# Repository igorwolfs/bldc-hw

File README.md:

# bldc

### NOTES
Replace the high power resistors C25468, minimum order quantity is 400+

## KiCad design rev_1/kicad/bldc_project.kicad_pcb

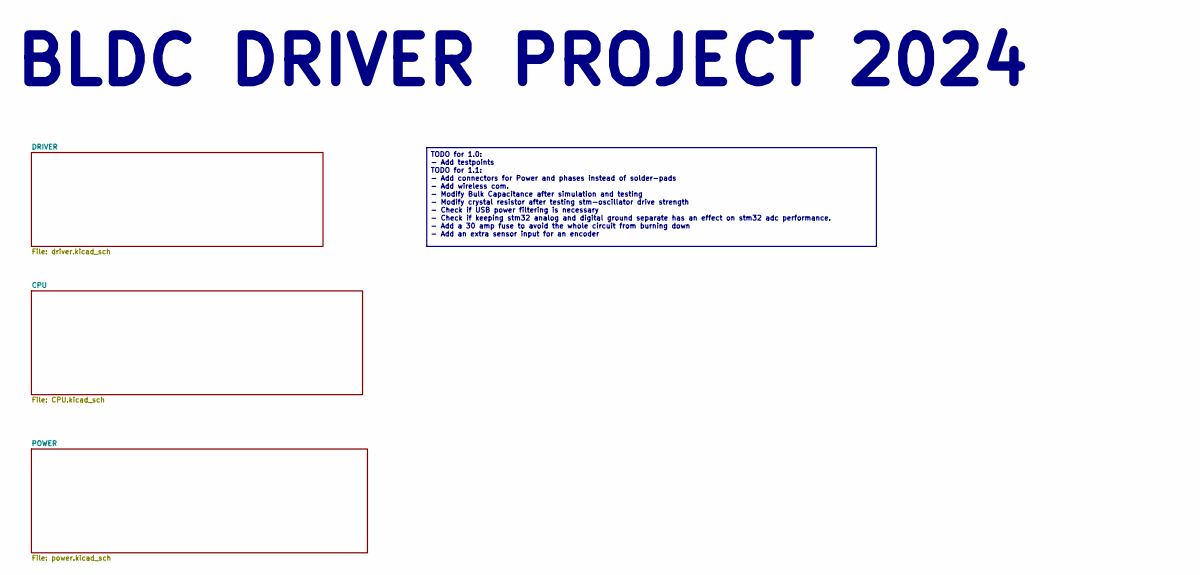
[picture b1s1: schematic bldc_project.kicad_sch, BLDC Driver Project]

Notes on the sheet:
BLDC DRIVER PROJECT 2024
TODO for 1.0: - Add testpoints TODO for 1.1: - Add connectors for Power and phases instead of solder-pads - Add wireless com. - Modify Bulk Capacitance after simulation and testing - Modify crystal resistor after testing stm-oscillator drive strength - Check if USB power filtering is necessary - Ch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

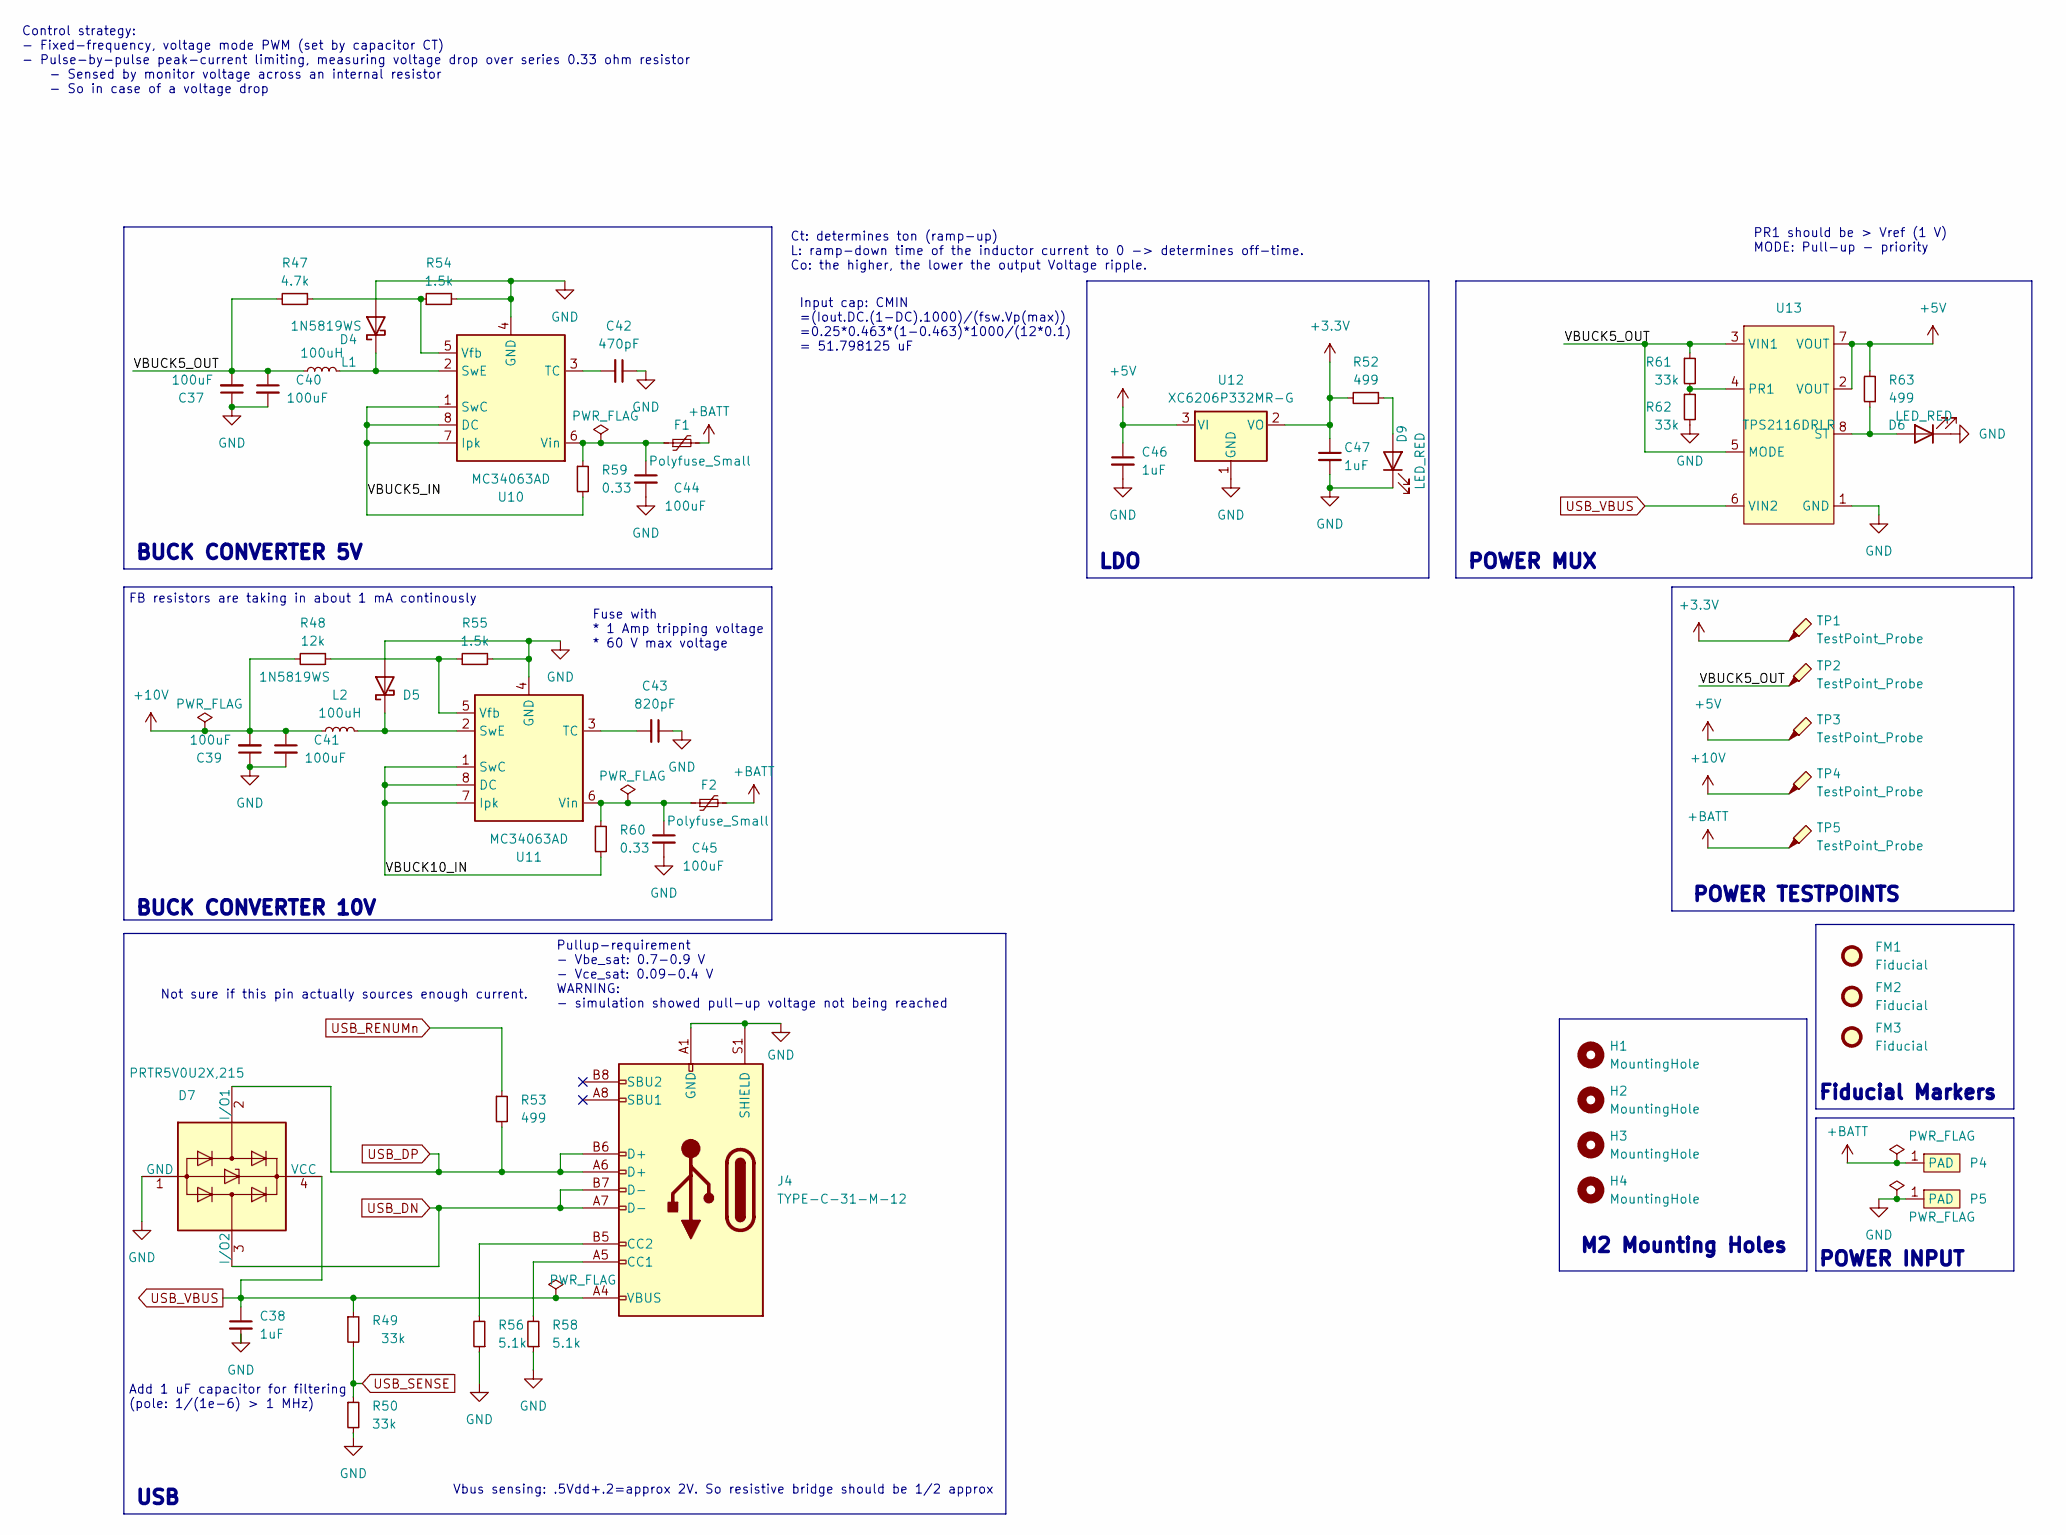
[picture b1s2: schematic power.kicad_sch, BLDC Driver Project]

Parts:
C37, C39, C40, C41, C44, C45: 100uF; C_1210_3225Metric; Manufacturing part numb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 CA55-B6R3M107T; LCSC Part Number C568913
C38, C46, C47: 1uF; C_1206_3216Metric; Manufacturing part numb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 CL31B105KBHNNNE; LCSC Part Number C1848
C42: 470pF; C_0603_1608Metric; Manufacturing part numb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 0603B471K500NT; LCSC Part Number C1620
C43: 820pF; C_0805_2012Metric_Pad1.18x1.45mm_HandSolder; Manufacturing part numb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 CL21B821KBANNNC; LCSC Part Number C296722
D4, D5: 1N5819WS; D_SOD-323; Manufacturing part numb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 1N5819WS; LCSC Part Number C191023
D6, D9: LED_RED; LED_0603_1608Metric; Manufacturing part numb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 F.0603.00139/P2-0603R1TS2-06T-002; LCSC Part Number C7496820
D7: PRTR5V0U2X,215; SOT-143; Manufacturing part numb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 PRTR5V0U2X,215; LCSC Part Number C12333
F1, F2: Polyfuse_Small; Fuse_1812_4532Metric; Manufacturing part numb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 BSMD1812-050-60V; LCSC Part Number C883142
FM1, FM2, FM3: Fiducial; Fiducial_1mm_Mask2mm
H1, H2, H3, H4: MountingHole; MountingHole_1.152mm_jlcpcb
J4: TYPE-C-31-M-12; USB_C_Receptacle_HRO_TYPE-C-31-M-12; Manufacturing part numb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 TYPE-C-31-M-12; LCSC Part Number C165948
L1, L2: 100uH; L_Sunlord_SWPA6045S; Manufacturing part numb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 SWPA6045S101MT; LCSC Part Number C60633
P4, P5: SolderWirePad_1x01_SMD_5x10mm
R47: 4.7k; R_0805_2012Metric; Manufacturing part numb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 0805W8F4701T5E; LCSC Part Number C17673
R48: 12k; R_0603_1608Metric; Manufacturing part numb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 0603WAF1202T5E; LCSC Part Number C22790
R49, R50, R61, R62: 33k; R_0603_1608Metric; Manufacturing part numb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 0603WAF3302T5E; LCSC Part Number C4216
R52, R53, R63: 499; R_0402_1005Metric; Manufacturing part numb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 0402WGF4990TCE; LCSC Part Number C4125
R54, R55: 1.5k; R_0805_2012Metric; Manufacturing part numb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 0805W8F1501T5E; LCSC Part Number C4310
R56, R58: 5.1k; R_0805_2012Metric; Manufacturing part numb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 0805W8F5101T5E; LCSC Part Number C27834
R59, R60: 0.33; R_1206_3216Metric; Manufacturing part numb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 1206W4J033KT5E; LCSC Part Number C25347
TP1, TP2, TP3, TP4, TP5: TestPoint_Probe; TestPoint_THTPad_D1.0mm_Drill0.5mm
U10, U11: MC34063AD; SOIC-8_3.9x4.9mm_P1.27mm; Manufacturing part numb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 MC34063; LCSC Part Number C5349988
U12: XC6206P332MR-G; SOT-23; Manufacturing part numb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 XC6206P332MR-G; LCSC Part Number C5446
U13: TPS2116DRLR; SOT-583-8; Manufacturing part numb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 TPS2116DRLR; LCSC Part Number C3235557

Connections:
+3.3V: C47.1, R52.2, TP1.1, U12.2 (VO); also elsewhere on the board
+5V: C46.1, R63.2, TP3.1, U12.3 (VI), U13.2 (VOUT), U13.7 (VOUT); also elsewhere on the board
+10V: C39.2, C41.1, L2.1, R48.2, TP4.1; also elsewhere on the board
+BATT: F1.2, F2.2, P4.1 (PAD), TP5.1; also elsewhere on the board
/POWER/VBUCK5_IN: R59.2, U10.1 (SwC), U10.7 (Ipk), U10.8 (DC)
/POWER/VBUCK5_OUT: C37.2, C40.1, L1.1, R47.2, R61.1, TP2.1, U13.3 (VIN1), U13.5 (MODE)
/POWER/VBUCK10_IN: R60.2, U11.1 (SwC), U11.7 (Ipk), U11.8 (DC)
GND: C37.1, C38.2, C39.1, C40.2, C41.2, C42.1, C43.1, C44.2, C45.2, C46.2, C47.2, D4.2 (A), D5.2 (A), D6.1 (K), D7.1 (GND), D9.1 (K), J4.A1 (GND), J4.A12 (GND), J4.B1 (GND), J4.B12 (GND), J4.S1 (SHIELD), P5.1 (PAD), R50.2, R54.2, R55.2, R56.1, R58.1, R62.2, U10.4 (GND), U11.4 (GND), U12.1 (GND), U13.1 (GND); also elsewhere on the board
unnamed: D4.1 (K), L1.2, U10.2 (SwE)
unnamed: D5.1 (K), L2.2, U11.2 (SwE)
unnamed: D6.2 (A), R63.1, U13.8 (ST)
unnamed: D9.2 (A), R52.1
unnamed: J4.A5 (CC1), R58.2
unnamed: J4.B5 (CC2), R56.2
unnamed: C42.2, U10.3 (TC)
unnamed: R47.1, R54.1, U10.5 (Vfb)
unnamed: C44.1, F1.1, R59.1, U10.6 (Vin)
unnamed: C43.2, U11.3 (TC)
unnamed: R48.1, R55.1, U11.5 (Vfb)
unnamed: C45.1, F2.1, R60.1, U11.6 (Vin)
unnamed: R61.2, R62.1, U13.4 (PR1)
USB_DN: D7.3 (I/O2), J4.A7 (D-), J4.B7 (D-); also elsewhere on the board
USB_DP: D7.2 (I/O1), J4.A6 (D+), J4.B6 (D+), R53.2; also elsewhere on the board
USB_RENUMn: R53.1; also elsewhere on the board
USB_SENSE: R49.2, R50.1; also elsewhere on the board
USB_VBUS: C38.1, D7.4 (VCC), J4.A4 (VBUS), J4.A9 (VBUS), J4.B4 (VBUS), J4.B9 (VBUS), R49.1, U13.6 (VIN2); also elsewhere on the board

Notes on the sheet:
PR1 should be > Vref (1 V) MODE: Pull-up - priority
Pullup-requirement - Vbe_sat: 0.7-0.9 V - Vce_sat: 0.09-0.4 V WARNING: - simulation showed pull-up voltage not being reached
Vbus sensing: .5Vdd+.2=approx 2V. So resistive bridge should be 1/2 approx
Not sure if this pin actually sources enough current.
Add 1 uF capacitor for filtering (pole: 1/(1e-6) > 1 MHz)
FB resistors are taking in about 1 mA continously
Fuse with * 1 Amp tripping voltage * 60 V max voltage
Input cap: CMIN =(Iout.DC.(1-DC).1000)/(fsw.Vp(max)) =0.25*0.463*(1-0.463)*1000/(12*0.1) = 51.798125 uF
Ct: determines ton (ramp-up) L: ramp-down time of the inductor current to 0 -> determines off-time. Co: the higher, the lower the output Voltage ripple.
Control strategy: - Fixed-frequency, voltage mode PWM (set by capacitor CT) - Pulse-by-pulse peak-current limiting, measuring voltage drop over series 0.33 ohm resistor - Sensed by monitor voltage across an internal resistor - So in case of a voltage drop
POWER INPUT
USB
Fiducial Markers
POWER TESTPOINTS
LDO
POWER MUX
BUCK CONVERTER 5V
BUCK CONVERTER 10V
M2 Mounting Holes

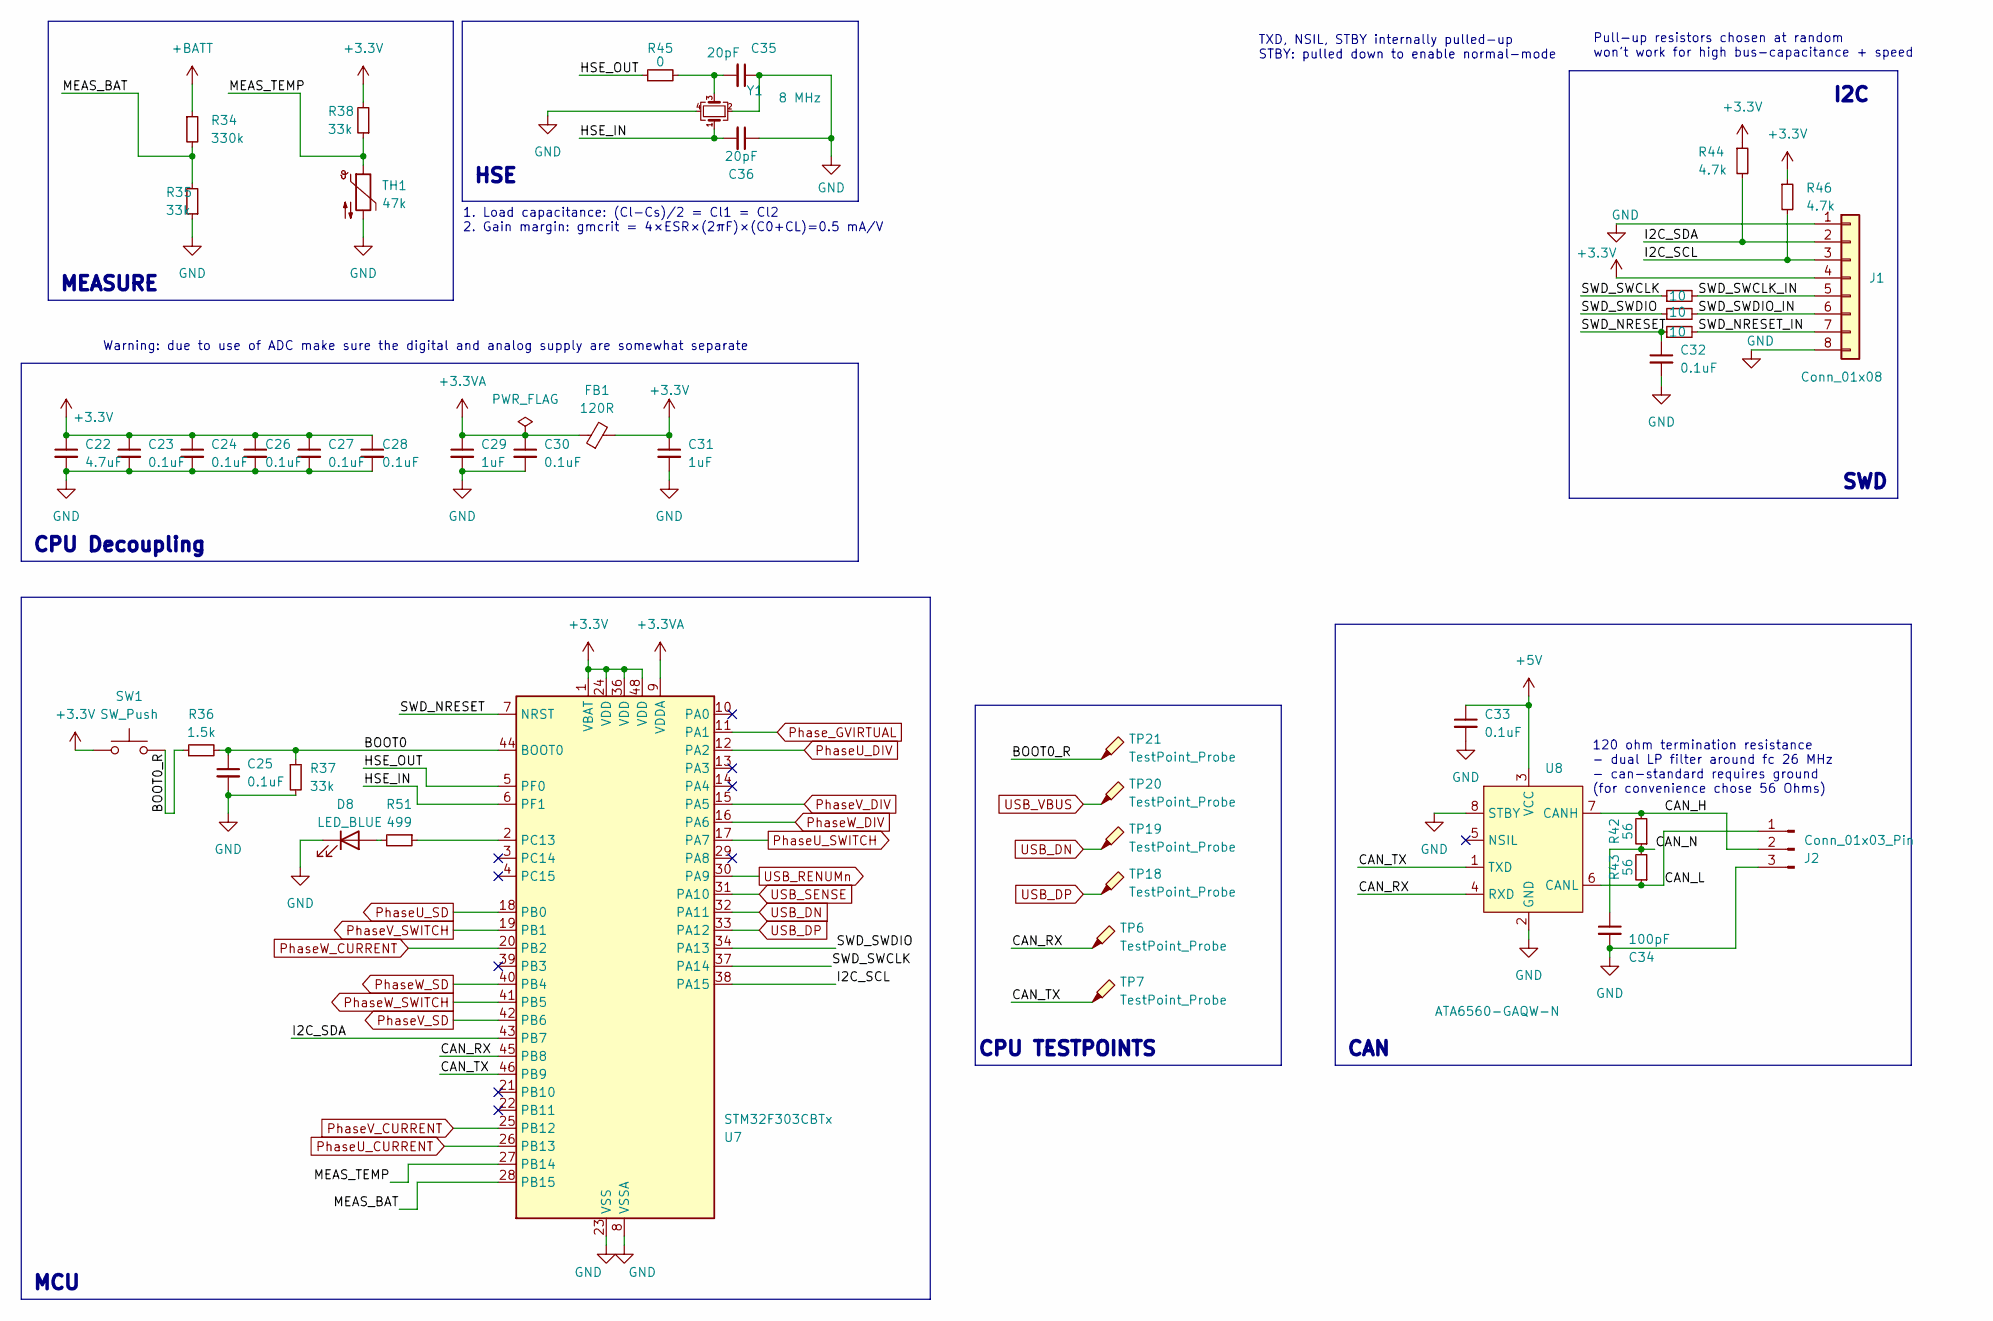
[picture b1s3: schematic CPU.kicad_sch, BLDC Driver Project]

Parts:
C22: 4.7uF; C_0603_1608Metric; Manufacturing part numb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 CL10A475KO8NNNC; LCSC Part Number C19666
C23, C24, C25, C26, C27, C28, C30, C32, C33: 0.1uF; C_0402_1005Metric; Manufacturing part numb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 CL05B104KB54PNC; LCSC Part Number C307331
C29, C31: 1uF; C_1206_3216Metric; Manufacturing part numb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 CL31B105KBHNNNE; LCSC Part Number C1848
C34: 100pF; C_0603_1608Metric; Manufacturing part numb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 CL10C101JB8NNNC; LCSC Part Number C14858
C35, C36: 20pF; C_0603_1608Metric; Manufacturing part numb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 CL10C200JB81PNC; LCSC Part Number C346210
D8: LED_BLUE; LED_0603_1608Metric; Manufacturing part numb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 F.0603.00026/P2-0603B1TS2-06T-001; LCSC Part Number C7496819
FB1: 120R; R_0603_1608Metric; Manufacturing part numb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 BLM18PG121SN1D; LCSC Part Number C14709
J1: Conn_01x08; PinHeader_1x08_P2.54mm_Vertical; Manufacturing part numb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 HB-PH3-25418PB2GOP; LCSC Part Number C6332201
J2: Conn_01x03_Pin; PinHeader_1x03_P2.54mm_Vertical; Manufacturing part numb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 HB-PH3-25413PB2GOP; LCSC Part Number C6332196
R34: 330k; R_0603_1608Metric; Manufacturing part numb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 0603WAF3303T5E; LCSC Part Number C23137
R35, R37, R38: 33k; R_0603_1608Metric; Manufacturing part numb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 0603WAF3302T5E; LCSC Part Number C4216
R36: 1.5k; R_0805_2012Metric; Manufacturing part numb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 0805W8F1501T5E; LCSC Part Number C4310
R41, R57, R64: 10; R_0402_1005Metric; Manufacturing part numb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 0402WGF100JTCE; LCSC Part Number C25077
R42, R43: 56; R_0603_1608Metric; Manufacturing part numb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 0603WAD560JT5E; LCSC Part Number C423025
R44, R46: 4.7k; R_0805_2012Metric; Manufacturing part numb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 0805W8F4701T5E; LCSC Part Number C17673
R45: 0; R_0402_1005Metric_Pad0.72x0.64mm_HandSolder; Manufacturing part numb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 0402WGF0000TCE; LCSC Part Number C17168
R51: 499; R_0402_1005Metric; Manufacturing part numb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 0402WGF4990TCE; LCSC Part Number C4125
SW1: SW_Push; TS-1088_w4.00xD3.00; Manufacturing part numb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 TS-1088-AR02016; LCSC Part Number C720477
TH1: 47k; R_0402_1005Metric; Manufacturing part numb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 SDNT1005X473F4050FTF; LCSC Part Number C279702
TP6, TP7, TP18, TP19, TP20, TP21: TestPoint_Probe; TestPoint_THTPad_D1.0mm_Drill0.5mm
U7: STM32F303CBTx; LQFP-48_7x7mm_P0.5mm; Manufacturing part numb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 STM32F303CBT6; LCSC Part Number C108516
U8: ATA6560-GAQW-N; SOIC-8-N8_3.9x4.9mm_P1.27mm; Manufacturing part numb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 ATA6560-GAQW-N; LCSC Part Number C2671262
Y1: 8 MHz; Crystal_SMD_3225-4Pin_3.2x2.5mm; Manufacturing part numb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 7325-0800A2010-00; LCSC Part Number C389817

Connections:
+3.3V: C22.1, C23.1, C24.1, C26.1, C27.1, C28.1, C31.1, FB1.2, J1.4, R38.2, R44.1, R46.1, SW1.1, U7.1 (VBAT), U7.24 (VDD), U7.36 (VDD), U7.48 (VDD); also elsewhere on the board
+3.3VA: C29.1, C30.1, FB1.1, U7.9 (VDDA)
+5V: C33.1, U8.3 (VCC); also elsewhere on the board
+BATT: R34.1; also elsewhere on the board
/CPU/BOOT0: C25.1, R36.2, R37.1, U7.44 (BOOT0)
/CPU/BOOT0_R: R36.1, SW1.2, TP21.1
/CPU/CAN_H: J2.2, R42.2, U8.7 (CANH)
/CPU/CAN_L: J2.1, R43.1, U8.6 (CANL)
/CPU/CAN_N: C34.1, R42.1, R43.2
/CPU/CAN_RX: TP6.1, U7.45 (PB8), U8.4 (RXD)
/CPU/CAN_TX: TP7.1, U7.46 (PB9), U8.1 (TXD)
/CPU/HSE_IN: C36.2, U7.6 (PF1), Y1.1
/CPU/HSE_OUT: R45.1, U7.5 (PF0)
/CPU/I2C_SCL: J1.3, R46.2, U7.38 (PA15)
/CPU/I2C_SDA: J1.2, R44.2, U7.43 (PB7)
/CPU/MEAS_BAT: R34.2, R35.2, U7.28 (PB15)
/CPU/MEAS_TEMP: R38.1, TH1.1, U7.27 (PB14)
/CPU/SWD_NRESET: C32.1, R41.1, U7.7 (NRST)
/CPU/SWD_NRESET_IN: J1.7, R41.2
/CPU/SWD_SWCLK: R57.1, U7.37 (PA14)
/CPU/SWD_SWCLK_IN: J1.5, R57.2
/CPU/SWD_SWDIO: R64.1, U7.34 (PA13)
/CPU/SWD_SWDIO_IN: J1.6, R64.2
GND: C22.2, C23.2, C24.2, C25.2, C26.2, C27.2, C28.2, C29.2, C30.2, C31.2, C32.2, C33.2, C34.2, C35.1, C36.1, D8.1 (K), J1.1, J1.8, J2.3, R35.1, R37.2, TH1.2, U7.8 (VSSA), U7.23 (VSS), U7.35 (VSS), U7.47 (VSS), U8.2 (GND), U8.8 (STBY), Y1.2, Y1.4; also elsewhere on the board
unnamed: C35.2, R45.2, Y1.3
unnamed: D8.2 (A), R51.2
unnamed: R51.1, U7.2 (PC13)
PhaseU_CURRENT: U7.26 (PB13); also elsewhere on the board
PhaseU_DIV: U7.12 (PA2); also elsewhere on the board
PhaseU_SD: U7.18 (PB0); also elsewhere on the board
PhaseU_SWITCH: U7.17 (PA7); also elsewhere on the board
PhaseV_CURRENT: U7.25 (PB12); also elsewhere on the board
PhaseV_DIV: U7.15 (PA5); also elsewhere on the board
PhaseV_SD: U7.42 (PB6); also elsewhere on the board
PhaseV_SWITCH: U7.19 (PB1); also elsewhere on the board
PhaseW_CURRENT: U7.20 (PB2); also elsewhere on the board
PhaseW_DIV: U7.16 (PA6); also elsewhere on the board
PhaseW_SD: U7.40 (PB4); also elsewhere on the board
PhaseW_SWITCH: U7.41 (PB5); also elsewhere on the board
Phase_GVIRTUAL: U7.11 (PA1); also elsewhere on the board
USB_DN: TP19.1, U7.32 (PA11); also elsewhere on the board
USB_DP: TP18.1, U7.33 (PA12); also elsewhere on the board
USB_RENUMn: U7.30 (PA9); also elsewhere on the board
USB_SENSE: U7.31 (PA10); also elsewhere on the board
USB_VBUS: TP20.1; also elsewhere on the board

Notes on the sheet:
TXD, NSIL, STBY internally pulled-up STBY: pulled down to enable normal-mode
Pull-up resistors chosen at random won't work for high bus-capacitance + speed
1. Load capacitance: (Cl-Cs)/2 = Cl1 = Cl2 2. Gain margin: gmcrit = 4×ESR×(2πF)×(C0+CL)=0.5 mA/V
Warning: due to use of ADC make sure the digital and analog supply are somewhat separate
120 ohm termination resistance - dual LP filter around fc 26 MHz - can-standard requires ground (for convenience chose 56 Ohms)
MEASURE
HSE
MCU
CPU Decoupling
SWD
CPU TESTPOINTS
I2C
CAN

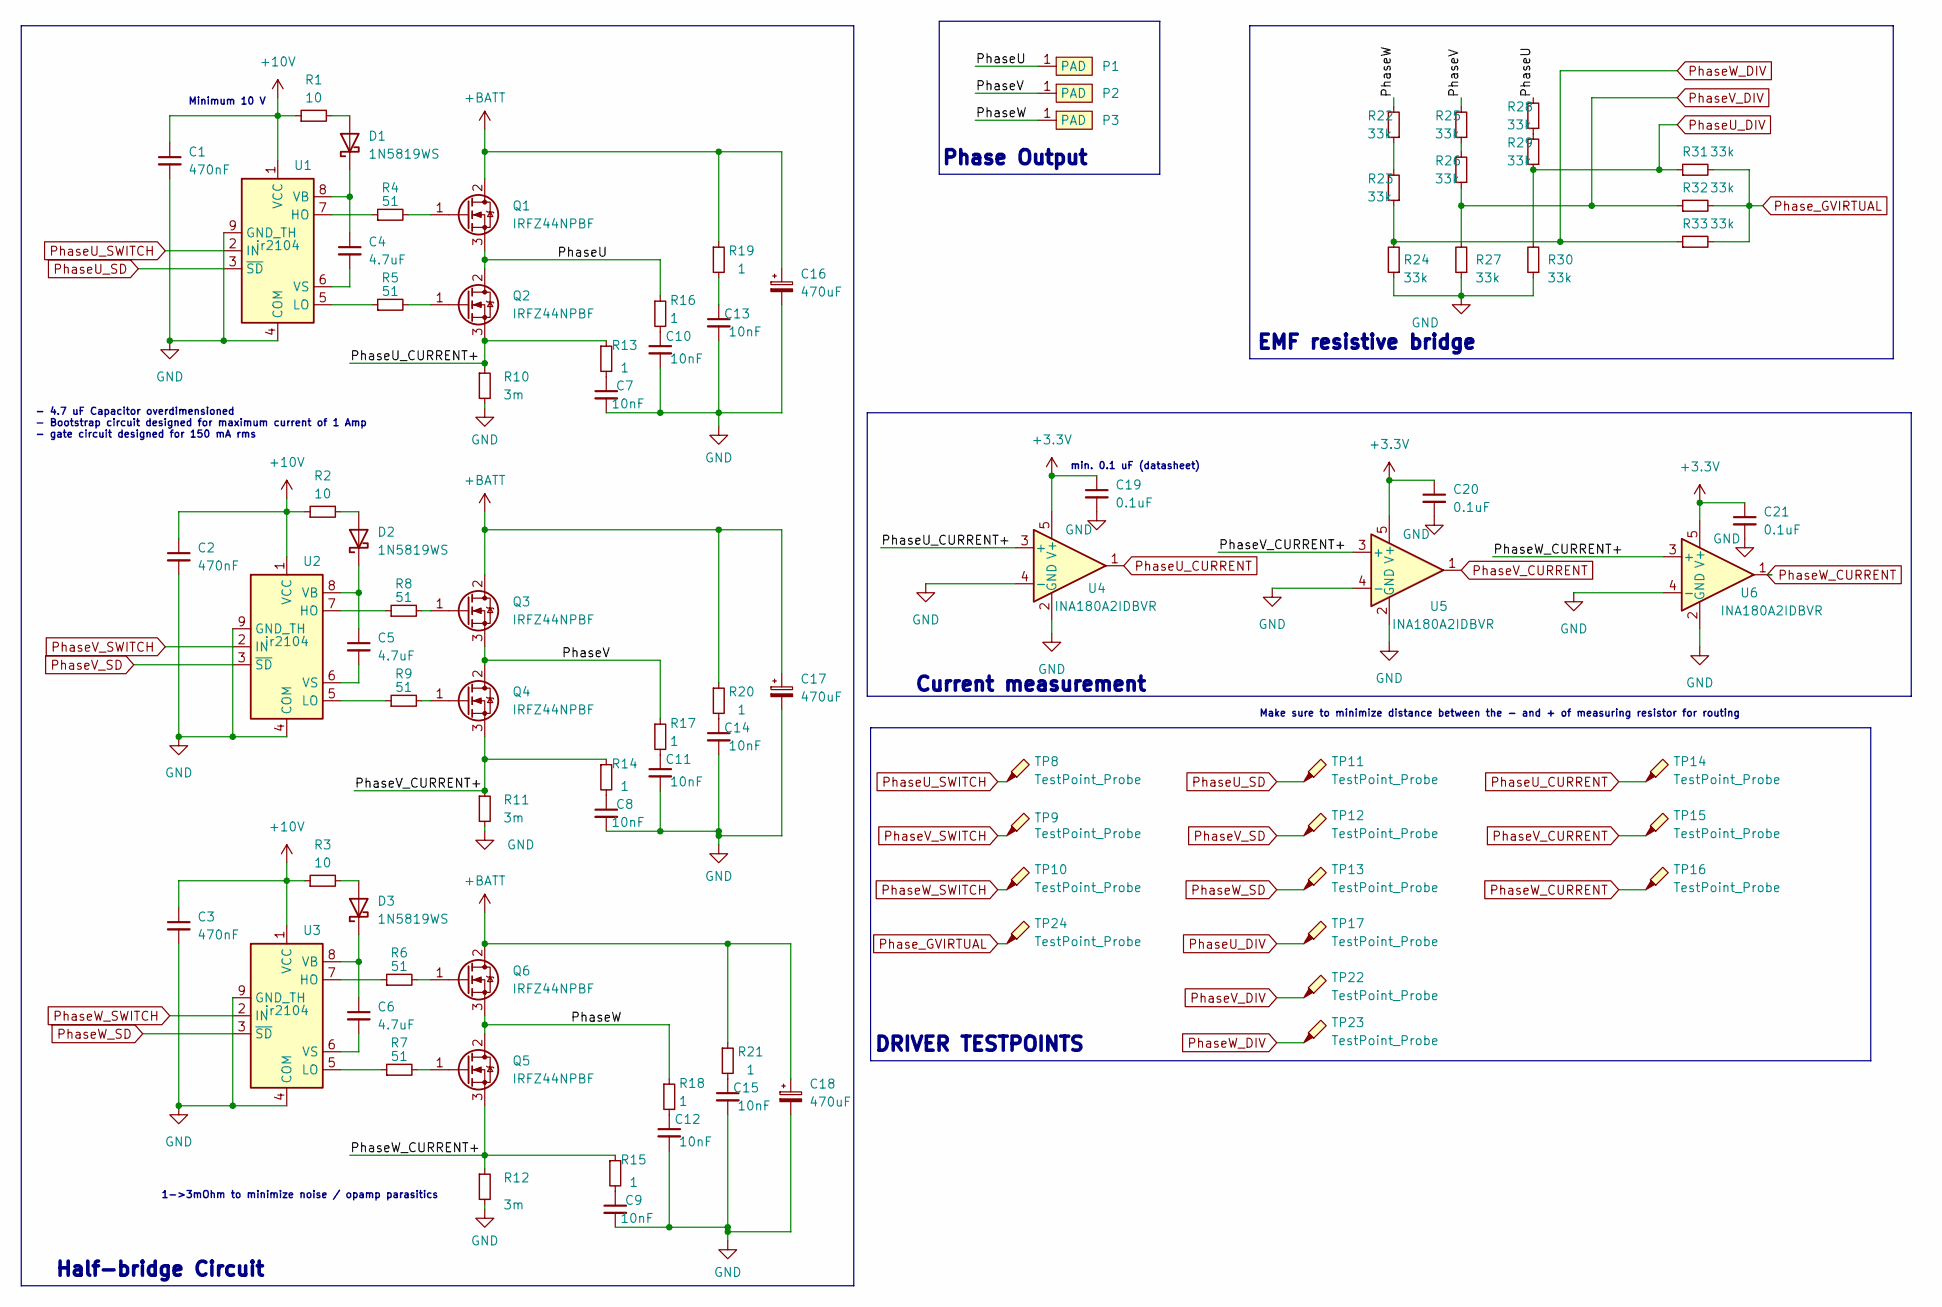
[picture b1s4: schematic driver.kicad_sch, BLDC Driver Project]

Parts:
C1, C2, C3: 470nF; C_0603_1608Metric; Manufacturing part numb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 CL10B474KA8NNNC; LCSC Part Number C1623
C4, C5, C6: 4.7uF; C_0603_1608Metric; Manufacturing part numb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 CL10A475KO8NNNC; LCSC Part Number C19666
C7, C8, C9, C10, C11, C12, C13, C14, C15: 10nF; C_0402_1005Metric; Manufacturing part numb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 CL05B103KB5NNNC; LCSC Part Number C15195
C16, C17, C18: 470uF; C_Radial_D10.0mm_H20.0mm_P5.00mm; Manufacturing part numb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 ERS1HM471G20OT; LCSC Part Number C106666
C19, C20, C21: 0.1uF; C_0402_1005Metric; Manufacturing part numb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 CL05B104KB54PNC; LCSC Part Number C307331
D1, D2, D3: 1N5819WS; D_SOD-323; Manufacturing part numb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 1N5819WS; LCSC Part Number C191023
P1, P2, P3: SolderWirePad_1x01_SMD_5x10mm
Q1, Q2, Q3, Q4, Q5, Q6: IRFZ44NPBF; TO-220-3_Vertical; Manufacturing part numb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 IRFZ44NPBF; LCSC Part Number C2586
R1, R2, R3: 10; R_1206_3216Metric; Manufacturing part numb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 1206W4F100JT5E; LCSC Part Number C17903
R4, R5, R6, R7, R8, R9: 51; R_1206_3216Metric; Manufacturing part numb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 1206W4F510JT5E; LCSC Part Number C18019
R10, R11, R12: 3m; R_2512_6332Metric; Manufacturing part numb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 LR2512D-2W-3mR-1%; LCSC Part Number C500615
R13, R14, R15, R16, R17, R18, R19, R20, R21: 1; R_0603_1608Metric; Manufacturing part numb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 0603WAF100KT5E; LCSC Part Number C22936
R22, R23, R24, R25, R26, R27, R28, R29, R30, R31, R32, R33: 33k; R_0603_1608Metric; Manufacturing part numb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 0603WAF3302T5E; LCSC Part Number C4216
TP8, TP9, TP10, TP11, TP12, TP13, TP14, TP15, TP16, TP17, TP22, TP23, TP24: TestPoint_Probe; TestPoint_THTPad_D1.0mm_Drill0.5mm
U1, U2, U3: ir2104; SOIC-8-1EP_3.9x4.9mm_P1.27mm_EP2.29x3mm; Manufacturing part numb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 IR2104STRPBF-JSM; LCSC Part Number C5804631
U4, U5, U6: INA180A2IDBVR; SOT-23-5; Manufacturing part numb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 INA180A2IDBVR; LCSC Part Number C192764

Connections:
+3.3V: C19.1, C20.1, C21.1, U4.5 (V+), U5.5 (V+), U6.5 (V+); also elsewhere on the board
+10V: C1.1, C2.1, C3.1, R1.1, R2.1, R3.1, U1.1 (VCC), U2.1 (VCC), U3.1 (VCC); also elsewhere on the board
+BATT: C16.1, C17.1, C18.1, Q1.2 (D), Q3.2 (D), Q6.2 (D), R19.1, R20.1, R21.1; also elsewhere on the board
/DRIVER/PhaseU: P1.1 (PAD), Q1.3 (S), Q2.2 (D), R16.1, R28.2
/DRIVER/PhaseU_CURRENT+: Q2.3 (S), R10.1, R13.1, U4.3 (+)
/DRIVER/PhaseV: P2.1 (PAD), Q3.3 (S), Q4.2 (D), R17.1, R25.2
/DRIVER/PhaseV_CURRENT+: Q4.3 (S), R11.1, R14.1, U5.3 (+)
/DRIVER/PhaseW: P3.1 (PAD), Q5.2 (D), Q6.3 (S), R18.1, R22.2
/DRIVER/PhaseW_CURRENT+: Q5.3 (S), R12.1, R15.1, U6.3 (+)
GND: C1.2, C2.2, C3.2, C7.2, C8.2, C9.2, C10.2, C11.2, C12.2, C13.2, C14.2, C15.2, C16.2, C17.2, C18.2, C19.2, C20.2, C21.2, R10.2, R11.2, R12.2, R24.1, R27.1, R30.1, U1.4 (COM), U1.9 (GND_TH), U2.4 (COM), U2.9 (GND_TH), U3.4 (COM), U3.9 (GND_TH), U4.2 (GND), U4.4 (-), U5.2 (GND), U5.4 (-), U6.2 (GND), U6.4 (-); also elsewhere on the board
unnamed: C7.1, R13.2
unnamed: C8.1, R14.2
unnamed: C9.1, R15.2
unnamed: C10.1, R16.2
unnamed: C11.1, R17.2
unnamed: C12.1, R18.2
unnamed: C13.1, R19.2
unnamed: C14.1, R20.2
unnamed: C15.1, R21.2
unnamed: D1.2 (A), R1.2
unnamed: C4.1, D1.1 (K), U1.8 (VB)
unnamed: D2.2 (A), R2.2
unnamed: C5.1, D2.1 (K), U2.8 (VB)
unnamed: D3.2 (A), R3.2
unnamed: C6.1, D3.1 (K), U3.8 (VB)
unnamed: Q1.1 (G), R4.2
unnamed: Q2.1 (G), R5.2
unnamed: Q3.1 (G), R8.2
unnamed: Q4.1 (G), R9.2
unnamed: Q5.1 (G), R7.2
unnamed: Q6.1 (G), R6.2
unnamed: R22.1, R23.2
unnamed: R25.1, R26.2
unnamed: R28.1, R29.2
unnamed: R4.1, U1.7 (HO)
unnamed: R5.1, U1.5 (LO)
unnamed: C4.2, U1.6 (VS)
unnamed: R8.1, U2.7 (HO)
unnamed: R9.1, U2.5 (LO)
unnamed: C5.2, U2.6 (VS)
unnamed: R6.1, U3.7 (HO)
unnamed: R7.1, U3.5 (LO)
unnamed: C6.2, U3.6 (VS)
PhaseU_CURRENT: TP14.1, U4.1; also elsewhere on the board
PhaseU_DIV: R29.1, R30.2, R31.1, TP17.1; also elsewhere on the board
PhaseU_SD: TP11.1, U1.3 (~SD); also elsewhere on the board
PhaseU_SWITCH: TP8.1, U1.2 (IN); also elsewhere on the board
PhaseV_CURRENT: TP15.1, U5.1; also elsewhere on the board
PhaseV_DIV: R26.1, R27.2, R32.1, TP22.1; also elsewhere on the board
PhaseV_SD: TP12.1, U2.3 (~SD); also elsewhere on the board
PhaseV_SWITCH: TP9.1, U2.2 (IN); also elsewhere on the board
PhaseW_CURRENT: TP16.1, U6.1; also elsewhere on the board
PhaseW_DIV: R23.1, R24.2, R33.1, TP23.1; also elsewhere on the board
PhaseW_SD: TP13.1, U3.3 (~SD); also elsewhere on the board
PhaseW_SWITCH: TP10.1, U3.2 (IN); also elsewhere on the board
Phase_GVIRTUAL: R31.2, R32.2, R33.2, TP24.1; also elsewhere on the board

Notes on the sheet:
Make sure to minimize distance between the - and + of measuring resistor for routing
min. 0.1 uF (datasheet)
Minimum 10 V
1->3mOhm to minimize noise / opamp parasitics
- 4.7 uF Capacitor overdimensioned - Bootstrap circuit designed for maximum current of 1 Amp - gate circuit designed for 150 mA rms
Half-bridge Circuit
Phase Output
DRIVER TESTPOINTS
EMF resistive bridge
Current measurement

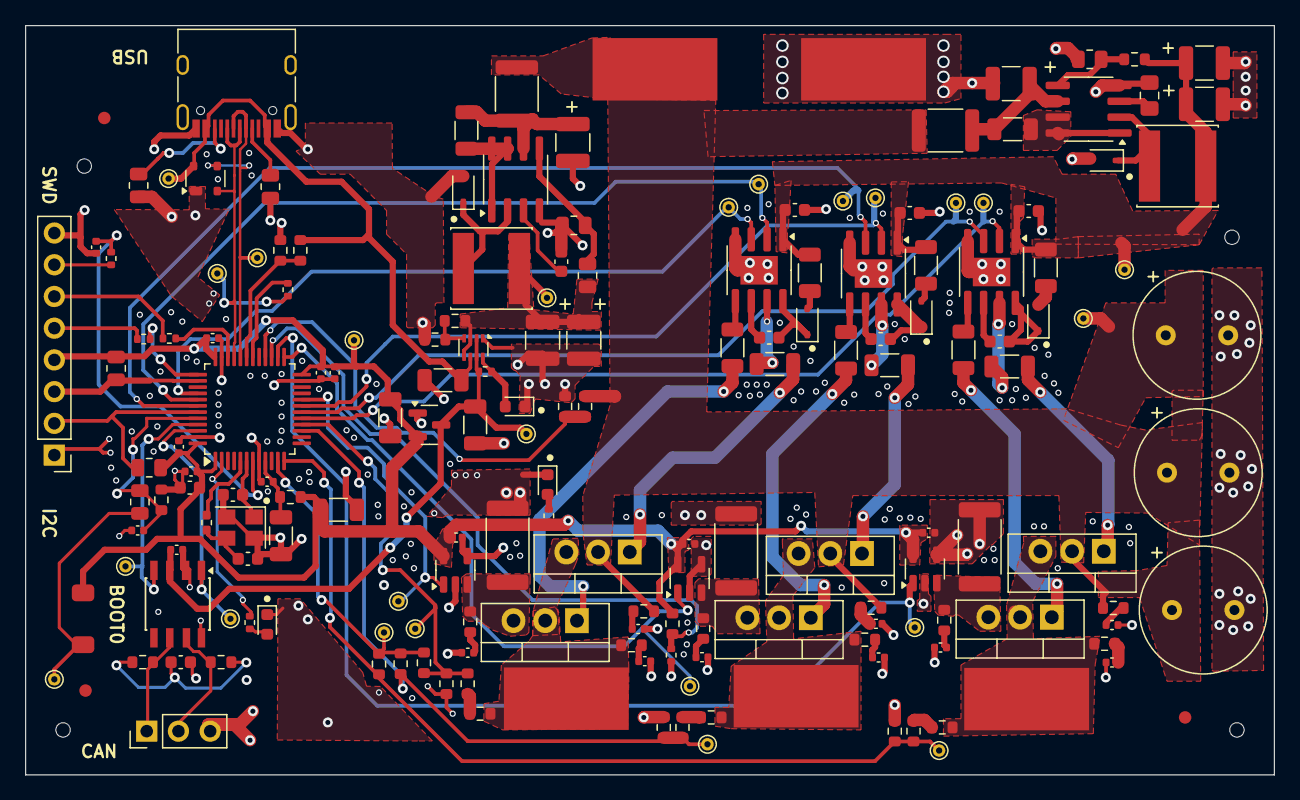
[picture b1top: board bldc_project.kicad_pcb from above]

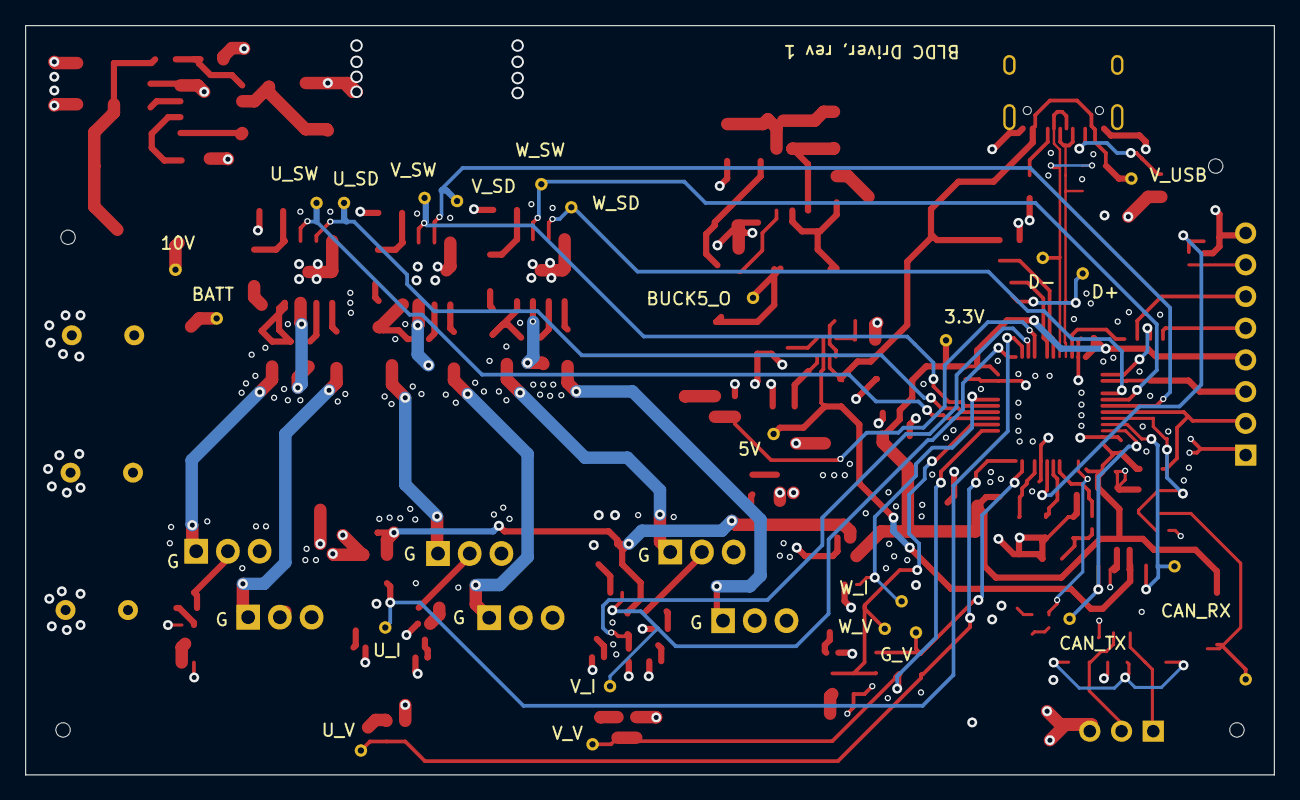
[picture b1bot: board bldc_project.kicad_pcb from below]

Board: 4 copper layers, 100.0 x 60.0 mm, 183 parts (24 on the bottom side), 101 nets.

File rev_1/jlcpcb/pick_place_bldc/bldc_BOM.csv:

Comment,Designator,Footprint,LCSC Part Number,Manufacturing part number
470pF,C42,Capacitor_SMD:C_0603_1608Metric,C1620,0603B471K500NT
470nF,"C1,C2,C3",Capacitor_SMD:C_0603_1608Metric,C1623,CL10B474KA8NNNC
1uF,"C29,C31,C38,C46,C47",Capacitor_SMD:C_1206_3216Metric,C1848,CL31B105KBHNNNE
IRFZ44NPBF,"Q1,Q2,Q3,Q4,Q5,Q6",Package_TO_SOT_THT:TO-220-3_Vertical,C2586,IRFZ44NPBF
499,"R51,R52,R53,R63",Resistor_SMD:R_0402_1005Metric,C4125,0402WGF4990TCE
33k,"R22,R23,R24,R25,R26,R27,R28,R29,R30,R31,R32,R33,R35,R37,R38,R49,R50,R61,R62",Resistor_SMD:R_0603_1608Metric,C4216,0603WAF3302T5E
1.5k,"R36,R54,R55",Resistor_SMD:R_0805_2012Metric,C4310,0805W8F1501T5E
XC6206P332MR-G,U12,Package_TO_SOT_SMD:SOT-23,C5446,XC6206P332MR-G
"PRTR5V0U2X,215",D7,Package_TO_SOT_SMD:SOT-143,C12333,"PRTR5V0U2X,215"
120R,FB1,Resistor_SMD:R_0603_1608Metric,C14709,BLM18PG121SN1D
100pF,C34,Capacitor_SMD:C_0603_1608Metric,C14858,CL10C101JB8NNNC
10nF,"C7,C8,C9,C10,C11,C12,C13,C14,C15",Capacitor_SMD:C_0402_1005Metric,C15195,CL05B103KB5NNNC
0,R45,Resistor_SMD:R_0402_1005Metric_Pad0.72x0.64mm_HandSolder,C17168,0402WGF0000TCE
4.7k,"R44,R46,R47",Resistor_SMD:R_0805_2012Metric,C17673,0805W8F4701T5E
10,"R1,R2,R3",Resistor_SMD:R_1206_3216Metric,C17903,1206W4F100JT5E
51,"R4,R5,R6,R7,R8,R9",Resistor_SMD:R_1206_3216Metric,C18019,1206W4F510JT5E
4.7uF,"C4,C5,C6,C22",Capacitor_SMD:C_0603_1608Metric,C19666,CL10A475KO8NNNC
12k,R48,Resistor_SMD:R_0603_1608Metric,C22790,0603WAF1202T5E
1,"R13,R14,R15,R16,R17,R18,R19,R20,R21",Resistor_SMD:R_0603_1608Metric,C22936,0603WAF100KT5E
330k,R34,Resistor_SMD:R_0603_1608Metric,C23137,0603WAF3303T5E
10,"R41,R57,R64",Resistor_SMD:R_0402_1005Metric,C25077,0402WGF100JTCE
0.33,"R59,R60",Resistor_SMD:R_1206_3216Metric,C25347,1206W4J033KT5E
5.1k,"R56,R58",Resistor_SMD:R_0805_2012Metric,C27834,0805W8F5101T5E
100uH,"L1,L2",L_Sunlord_SWPA6045S,C60633,SWPA6045S101MT
470uF,"C16,C17,C18",Capacitor_THT:C_Radial_D10.0mm_H20.0mm_P5.00mm,C106666,ERS1HM471G20OT
STM32F303CBTx,U7,Package_QFP:LQFP-48_7x7mm_P0.5mm,C108516,STM32F303CBT6
TYPE-C-31-M-12,J4,Connector_USB:USB_C_Receptacle_HRO_TYPE-C-31-M-12,C165948,TYPE-C-31-M-12
1N5819WS,"D1,D2,D3,D4,D5",Diode_SMD:D_SOD-323,C191023,1N5819WS
INA180A2IDBVR,"U4,U5,U6",Package_TO_SOT_SMD:SOT-23-5,C192764,INA180A2IDBVR
47k,TH1,Resistor_SMD:R_0402_1005Metric,C279702,SDNT1005X473F4050FTF
820pF,C43,Capacitor_SMD:C_0805_2012Metric_Pad1.18x1.45mm_HandSolder,C296722,CL21B821KBANNNC
0.1uF,"C19,C20,C21,C23,C24,C25,C26,C27,C28,C30,C32,C33",Capacitor_SMD:C_0402_1005Metric,C307331,CL05B104KB54PNC
20pF,"C35,C36",Capacitor_SMD:C_0603_1608Metric,C346210,CL10C200JB81PNC
8 MHz,Y1,Crystal:Crystal_SMD_3225-4Pin_3.2x2.5mm,C389817,7325-0800A2010-00
56,"R42,R43",Resistor_SMD:R_0603_1608Metric,C423025,0603WAD560JT5E
3m,"R10,R11,R12",Resistor_SMD:R_2512_6332Metric,C500615,LR2512D-2W-3mR-1%
100uF,"C37,C39,C40,C41,C44,C45",Capacitor_SMD:C_1210_3225Metric,C568913,CA55-B6R3M107T
SW_Push,SW1,bldc:TS-1088_w4.00xD3.00,C720477,TS-1088-AR02016 
Polyfuse_Small,"F1,F2",Fuse:Fuse_1812_4532Metric,C883142,BSMD1812-050-60V
ATA6560-GAQW-N,U8,bldc:SOIC-8-N8_3.9x4.9mm_P1.27mm,C2671262,ATA6560-GAQW-N
TPS2116DRLR,U13,Package_TO_SOT_SMD:SOT-583-8,C3235557,TPS2116DRLR
MC34063AD,"U10,U11",Package_SO:SOIC-8_3.9x4.9mm_P1.27mm,C5349988,MC34063
ir2104,"U1,U2,U3",Package_SO:SOIC-8-1EP_3.9x4.9mm_P1.27mm_EP2.29x3mm,C5804631,IR2104STRPBF-JSM
Conn_01x03_Pin,J2,Connector_PinHeader_2.54mm:PinHeader_1x03_P2.54mm_Vertical,C6332196,HB-PH3-25413PB2GOP 
Conn_01x08,J1,Connector_PinHeader_2.54mm:PinHeader_1x08_P2.54mm_Vertical,C6332201,HB-PH3-25418PB2GOP 
LED_BLUE,D8,LED_SMD:LED_0603_1608Metric,C7496819,F.0603.00026/P2-0603B1TS2-06T-001
LED_RED,"D6,D9",LED_SMD:LED_0603_1608Metric,C7496820,F.0603.00139/P2-0603R1TS2-06T-002
